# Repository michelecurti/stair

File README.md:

# stair

Switch on a stair that for every step has a strip led, 
controlled in PWM.
All this to generate a stair "wave effect" for my sister.

## project structure

under hw there is the hardware
under fw there is the firmware

Meh..

## software requirements

I worked on OpenBSD.

For the hardware I used Kicad, for the firmware, vim + Makefile..

The toolchain is arm-none-eabi-gcc-linaro.

The "core" is the STM32 BluePill, some shift registers and some
mosfets..

To debug the board I used the st-link with openocd.

## how to compile

$ cd fw/stair/
$ make

## how to debug

$ make debug

## image

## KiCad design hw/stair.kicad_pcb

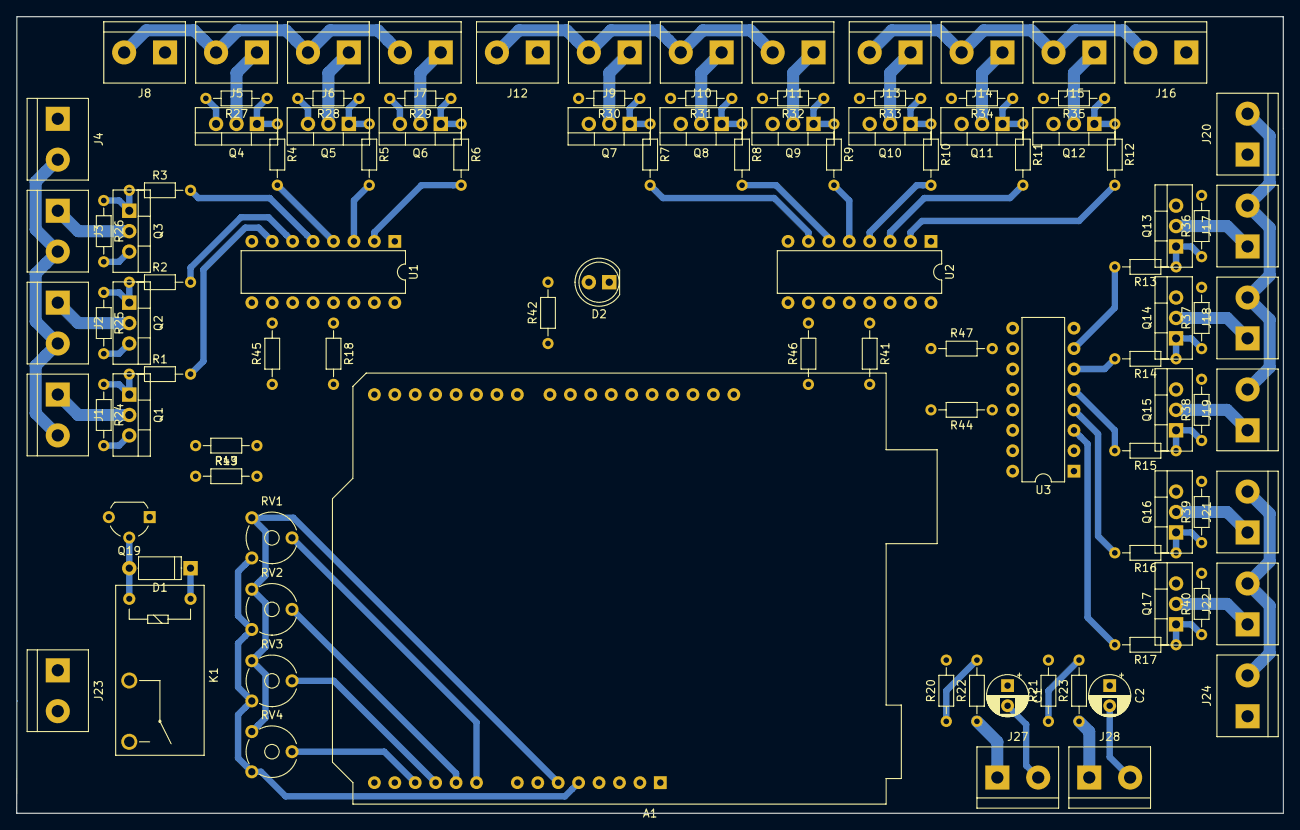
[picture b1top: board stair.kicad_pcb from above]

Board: 2 copper layers, 157.5 x 99.1 mm, 104 parts (0 on the bottom side), 87 nets.

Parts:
A1: AR; Arduino_UNO_R3
C1, C2: C; CP_Radial_D5.0mm_P2.50mm
D1: D; D_A-405_P7.62mm_Horizontal
D2: LED; LED_D5.0mm
J1: M1; TerminalBlock_bornier-2_P5.08mm
J2: M2; TerminalBlock_bornier-2_P5.08mm
J3, J17: M3; TerminalBlock_bornier-2_P5.08mm
J4: P1; TerminalBlock_bornier-2_P5.08mm
J5: M4; TerminalBlock_bornier-2_P5.08mm
J6: M5; TerminalBlock_bornier-2_P5.08mm
J7: M6; TerminalBlock_bornier-2_P5.08mm
J8: P2; TerminalBlock_bornier-2_P5.08mm
J9: M7; TerminalBlock_bornier-2_P5.08mm
J10: M8; TerminalBlock_bornier-2_P5.08mm
J11: M9; TerminalBlock_bornier-2_P5.08mm
J12: P3; TerminalBlock_bornier-2_P5.08mm
J13: M10; TerminalBlock_bornier-2_P5.08mm
J14: M11; TerminalBlock_bornier-2_P5.08mm
J15: M12; TerminalBlock_bornier-2_P5.08mm
J16: P4; TerminalBlock_bornier-2_P5.08mm
J18: M14; TerminalBlock_bornier-2_P5.08mm
J19: M15; TerminalBlock_bornier-2_P5.08mm
J20: P5; TerminalBlock_bornier-2_P5.08mm
J21: M16; TerminalBlock_bornier-2_P5.08mm
J22: M17; TerminalBlock_bornier-2_P5.08mm
J23: MR1; TerminalBlock_bornier-2_P5.08mm
J24: P6; TerminalBlock_bornier-2_P5.08mm
J27: MB2; TerminalBlock_bornier-2_P5.08mm
J28: MB1; TerminalBlock_bornier-2_P5.08mm
K1: G5Q-1A; Relay_SPST_OMRON-G5Q
Q1, Q2, Q3, Q4, Q5, Q6, Q7, Q8, Q9, Q10, Q11, Q12, Q13, Q14, Q15, Q16, Q17: IRF540N; TO-220-3_Vertical
Q19: Q_NPN_BCE; TO-92_Wide
R1, R2, R3, R4, R5, R6, R7, R8, R9, R10, R11, R12, R13, R14, R15, R16, R17, R18, R19, R20, R21, R22, R23, R24, R25, R26, R27, R28, R29, R30, R31, R32, R33, R34, R35, R36, R37, R38, R39, R40, R41, R42, R43, R44, R45, R46, R47: R; R_Axial_DIN0204_L3.6mm_D1.6mm_P7.62mm_Horizontal
RV1, RV2, RV3, RV4: 10K; Potentiometer_Trimmer_Piher_PT-6v_Horizontal
U1, U2, U3: 74HC595; DIP-16_W7.62mm

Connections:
+5V: A1.5, D1.1, K1.5, R45.1, R46.1, R47.1, RV1.1, RV2.1, RV3.1, RV4.1, U1.16, U2.16, U3.16
BTN1: A1.24, R20.2
BTN2: A1.25, R21.2
CKO: A1.26, U1.12, U2.12, U3.12
CLK: A1.28, U1.11, U2.11, U3.11
GND: A1.6, A1.7, A1.29, C1.2, C2.2, D2.1, J4.1, J8.1, J12.1, J16.1, J20.1, J24.1, J27.2, J28.2, Q1.3, Q2.3, Q3.3, Q4.3, Q5.3, Q6.3, Q7.3, Q8.3, Q9.3, Q10.3, Q11.3, Q12.3, Q13.3, Q14.3, Q15.3, Q16.3, Q17.3, Q19.3, R18.2, R24.2, R25.2, R26.2, R27.2, R28.2, R29.2, R30.2, R31.2, R32.2, R33.2, R34.2, R35.2, R36.2, R37.2, R38.2, R39.2, R40.2, R41.2, R43.1, R44.2, RV1.3, RV2.3, RV3.3, RV4.3, U1.8, U2.8, U3.8
LED1: R1.2, U1.7
LED2: R2.2, U1.6
LED3: R3.2, U1.5
LED4: R4.2, U1.4
LED5: R5.2, U1.3
LED6: R6.2, U1.2
LED7: R7.2, U2.7
LED8: R8.2, U2.6
LED9: R9.2, U2.5
LED10: R10.2, U2.4
LED11: R11.2, U2.3
LED12: R12.2, U2.2
LED13: R13.2, U3.7
LED14: R14.2, U3.6
LED15: R15.2, U3.5
LED16: R16.2, U3.4
LED17: R17.2, U3.3
MAX_PWM: A1.12, RV4.2
MOSI: A1.27, U1.14
unnamed: C1.1, R20.1, R22.2
unnamed: C2.1, R21.1, R23.2
unnamed: D1.2, K1.1, Q19.2
unnamed: D2.2, R42.2
unnamed: J1.1, Q1.2
unnamed: J1.2, J2.2, J3.2, J4.2
unnamed: J2.1, Q2.2
unnamed: J3.1, Q3.2
unnamed: J5.1, Q4.2
unnamed: J5.2, J6.2, J7.2, J8.2
unnamed: J6.1, Q5.2
unnamed: J7.1, Q6.2
unnamed: J9.1, Q7.2
unnamed: J10.1, Q8.2
unnamed: J9.2, J10.2, J11.2, J12.2
unnamed: J11.1, Q9.2
unnamed: J13.1, Q10.2
unnamed: J13.2, J14.2, J15.2, J16.2
unnamed: J14.1, Q11.2
unnamed: J15.1, Q12.2
unnamed: J17.1, Q13.2
unnamed: J17.2, J18.2, J19.2, J20.2
unnamed: J18.1, Q14.2
unnamed: J19.1, Q15.2
unnamed: J21.1, Q16.2
unnamed: J21.2, J22.2, J24.2
unnamed: J22.1, Q17.2
unnamed: J23.1, K1.2
unnamed: J23.2, K1.3
unnamed: J27.1, R22.1
unnamed: J28.1, R23.1
unnamed: Q1.1, R1.1, R24.1
unnamed: Q2.1, R2.1, R25.1
unnamed: Q3.1, R3.1, R26.1
unnamed: Q4.1, R4.1, R27.1
unnamed: Q5.1, R5.1, R28.1
unnamed: Q6.1, R6.1, R29.1
unnamed: Q7.1, R7.1, R30.1
unnamed: Q8.1, R8.1, R31.1
unnamed: Q9.1, R9.1, R32.1
unnamed: Q10.1, R10.1, R33.1
unnamed: Q11.1, R11.1, R34.1
unnamed: Q12.1, R12.1, R35.1
unnamed: Q13.1, R13.1, R36.1
unnamed: Q14.1, R14.1, R37.1
unnamed: Q15.1, R15.1, R38.1
unnamed: Q16.1, R16.1, R39.1
unnamed: Q17.1, R17.1, R40.1
unnamed: Q19.1, R19.1, R43.2
unnamed: R18.1, U1.13
unnamed: R41.1, U2.13
unnamed: R44.1, U3.13
unnamed: R45.2, U1.10
unnamed: R46.2, U2.10
unnamed: R47.2, U3.10
unnamed: U1.9, U2.14
unnamed: U2.9, U3.14
RDOWN: A1.10, RV2.2
REL: A1.22, R19.2
RUN: A1.23, R42.1
RUP: A1.9, RV1.2
TIME_ON: A1.11, RV3.2

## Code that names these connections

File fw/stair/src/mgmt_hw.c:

#include <string.h>
#include "stm32f1xx_hal.h"
#include "mgmt_hw.h"
#include "app.h"

#define ADC_CHS		(5)

/* buttons pins */
#define BTNX_GPIO_Port 	GPIOB
#define BTN1_Pin 	GPIO_PIN_0
#define BTN2_Pin 	GPIO_PIN_1
/* output pins */
#define LED_Pin 	GPIO_PIN_13
#define LED_GPIO_Port 	GPIOC
#define LDOUT_Pin 	GPIO_PIN_8
#define LDOUT_GPIO_Port GPIOA
#define RELAY_Pin 	GPIO_PIN_9
#define RELAY_GPIO_Port GPIOB
/* SPI pins*/

static volatile uint32_t ticks;
static uint8_t curr_adc;
static uint32_t adc_vals[ADC_CHS];

static const uint16_t counters[] = 
{
	160, 176, 193, 212, 232, 255, 280, 307, 338, 371, 407, 447, 
	490, 538, 591, 649, 712, 782, 858, 942, 1034, 1135, 1246, 
	1368, 1502, 1649, 1810, 1987, 2182, 2395, 2629, 2886, 3169, 
	3479, 3819, 4192, 4602, 5052, 5546, 6089, 6684, 7338, 8056, 
	8844, 9709, 10658, 11701, 12845, 14101, 15480, 16994, 
	18656, 20481, 22484, 24683, 27097, 29747, 32656, 35850, 
	39356, 43205, 47431, 52070, 57162, 
};

#define MAX_PWM		(sizeof(counters)/sizeof(counters[0]))

static uint8_t irq_cnt;
uint32_t pwms[LEDS_CNT];

static void Error_Handler(void)
{
	for (;;);
}

static void SystemClock_Config(void)
{
	RCC_OscInitTypeDef RCC_OscInitStruct = {0};
	RCC_ClkInitTypeDef RCC_ClkInitStruct = {0};
	RCC_PeriphCLKInitTypeDef PeriphClkInit = {0};

	/* Initializes the CPU, AHB and APB busses clocks */
	RCC_OscInitStruct.OscillatorType = RCC_OSCILLATORTYPE_HSE;
	RCC_OscInitStruct.HSEState = RCC_HSE_ON;
	RCC_OscInitStruct.HSEPredivValue = RCC_HSE_PREDIV_DIV1;
	RCC_OscInitStruct.HSIState = RCC_HSI_ON;
	RCC_OscInitStruct.PLL.PLLState = RCC_PLL_ON;
	RCC_OscInitStruct.PLL.PLLSource = RCC_PLLSOURCE_HSE;
	RCC_OscInitStruct.PLL.PLLMUL = RCC_PLL_MUL8;

	if (HAL_RCC_OscConfig(&RCC_OscInitStruct) != HAL_OK)
	{
		Error_Handler();
	}

	/* Initializes the CPU, AHB and APB busses clocks */
	RCC_ClkInitStruct.ClockType = RCC_CLOCKTYPE_HCLK |
		RCC_CLOCKTYPE_SYSCLK | RCC_CLOCKTYPE_PCLK1 | 
		RCC_CLOCKTYPE_PCLK2;
	RCC_ClkInitStruct.SYSCLKSource = RCC_SYSCLKSOURCE_PLLCLK;
	RCC_ClkInitStruct.AHBCLKDivider = RCC_SYSCLK_DIV1;
	RCC_ClkInitStruct.APB1CLKDivider = RCC_HCLK_DIV2;
	RCC_ClkInitStruct.APB2CLKDivider = RCC_HCLK_DIV1;

	if (HAL_RCC_ClockConfig(&RCC_ClkInitStruct, 
				FLASH_LATENCY_2) != HAL_OK)
	{
		Error_Handler();
	}

	PeriphClkInit.PeriphClockSelection = RCC_PERIPHCLK_ADC;
	PeriphClkInit.AdcClockSelection = RCC_ADCPCLK2_DIV4;

	if (HAL_RCCEx_PeriphCLKConfig(&PeriphClkInit) != HAL_OK)
	{
		Error_Handler();
	}
}

static void MX_SPI2_Init(void)
{
	/* enable clock */
	__HAL_RCC_SPI2_CLK_ENABLE();

	/* disable SPI2 */
	SPI2->CR1 &= SPI_CR1_SPE;

	/* set prescaler */
	SPI2->CR1 |= SPI_BAUDRATEPRESCALER_4;

	/* master mode */
	SPI2->CR1 |= SPI_MODE_MASTER;

	/* do not use slave select */
	SPI2->CR1 |= SPI_CR1_SSM;
	//SPI2->CR1 &= ~SPI_CR1_SSI;

	/* enable SPI2 */
	SPI2->CR1 |= SPI_CR1_SPE;
}

static void MX_GPIO_Init(void)
{
	GPIO_InitTypeDef GPIO_InitStruct = { 0 };

	/* GPIO Ports Clock Enable */
	__HAL_RCC_GPIOA_CLK_ENABLE();
	__HAL_RCC_GPIOB_CLK_ENABLE();
	__HAL_RCC_GPIOC_CLK_ENABLE();
	__HAL_RCC_GPIOD_CLK_ENABLE();

	/*Configure GPIO pin Output Level */
	HAL_GPIO_WritePin(LED_GPIO_Port, LED_Pin, GPIO_PIN_SET);

	/*Configure GPIO pin Output Level */
	HAL_GPIO_WritePin(LDOUT_GPIO_Port, LDOUT_Pin, GPIO_PIN_RESET);

	/*Configure GPIO pin : LED_Pin */
	GPIO_InitStruct.Pin = LED_Pin;
	GPIO_InitStruct.Mode = GPIO_MODE_OUTPUT_PP;
	GPIO_InitStruct.Pull = GPIO_NOPULL;
	GPIO_InitStruct.Speed = GPIO_SPEED_FREQ_LOW;
	HAL_GPIO_Init(LED_GPIO_Port, &GPIO_InitStruct);

	/*Configure GPIO pin : RELAY_Pin */
	GPIO_InitStruct.Pin = RELAY_Pin;
	GPIO_InitStruct.Mode = GPIO_MODE_OUTPUT_PP;
	GPIO_InitStruct.Pull = GPIO_NOPULL;
	GPIO_InitStruct.Speed = GPIO_SPEED_FREQ_LOW;
	HAL_GPIO_Init(RELAY_GPIO_Port, &GPIO_InitStruct);

	/*Configure GPIO pin : LDOUT_Pin  */
	GPIO_InitStruct.Pin = LDOUT_Pin;
	GPIO_InitStruct.Mode = GPIO_MODE_OUTPUT_PP;
	GPIO_InitStruct.Pull = GPIO_NOPULL;
	GPIO_InitStruct.Speed = GPIO_SPEED_FREQ_LOW;
	HAL_GPIO_Init(LDOUT_GPIO_Port, &GPIO_InitStruct);

	/*Configure GPIO pins : BTN1_Pin BTN2_Pin */
	GPIO_InitStruct.Pin = BTN1_Pin | BTN2_Pin;
	GPIO_InitStruct.Mode = GPIO_MODE_INPUT;
	GPIO_InitStruct.Pull = GPIO_PULLUP;
	HAL_GPIO_Init(BTNX_GPIO_Port, &GPIO_InitStruct);
	
	/* configure ADC pins */
	memset(&GPIO_InitStruct, 0, sizeof(GPIO_InitStruct));
	GPIO_InitStruct.Pin = GPIO_PIN_0 | GPIO_PIN_1 | GPIO_PIN_2 |
		GPIO_PIN_3 | GPIO_PIN_4;
	GPIO_InitStruct.Mode = GPIO_MODE_ANALOG;
	GPIOA->CRL &= 0xFFFFFC00;
	//HAL_GPIO_Init(GPIOA, &GPIO_InitStruct);

	/* configure SPI pins */
	GPIO_InitStruct.Pin = GPIO_PIN_13 | GPIO_PIN_15;
	GPIO_InitStruct.Mode = GPIO_MODE_AF_PP;
	GPIO_InitStruct.Speed = GPIO_SPEED_FREQ_HIGH;
	HAL_GPIO_Init(GPIOB, &GPIO_InitStruct);
}

static void MX_ADC1_Init(void)
{
	__HAL_RCC_ADC1_CLK_ENABLE();

	ADC1->CR2 |= ADC_CR2_ADON;
	while((ADC1->CR2 | ADC_CR2_ADON) == 0);
	ADC1->CR2 |= ADC_CR2_EXTSEL;

	ADC1->SMPR1 = 0x7FFFFFFF;
	ADC1->SMPR2 = 0xCFFFFFFF;
}

static void pwm_timer_init(void)
{
	/* enable clock */
	__HAL_RCC_TIM4_CLK_ENABLE();

	/* set prescaler */
	TIM4->PSC = 0;

	/* schedule first timer interrupt */
	TIM4->ARR = 0xFFFE;

	/* enable counter */
	TIM4->CR1 |= TIM_CR1_CEN;

	/* enable counter interrupt */
	TIM4->DIER |= TIM_DIER_UIE;

	/* enable TIM4 interrupt */
	NVIC_EnableIRQ(TIM4_IRQn);
}

void SysTick_Handler (void)
{
	HAL_IncTick();
}

void mgmt_hw_init(void)
{
	SystemClock_Config();
	//SystickInit(APP_TICK_FREQ);
	HAL_Init();
	MX_GPIO_Init();
	MX_SPI2_Init();
	MX_ADC1_Init();
	pwm_timer_init();
}

void mgmt_hw_fsm(void)
{
	static uint32_t old;
	uint32_t tick;

	tick = HAL_GetTick() / 50;

	if (tick != old)
	{
		old = tick;

		adc_vals[curr_adc] = (adc_vals[curr_adc] + ADC1->DR) / 2;

		if (++curr_adc >= ADC_CHS)
		{
			curr_adc = 0;
		}

		ADC1->SQR3 = (curr_adc << (0 * 5));
		ADC1->CR2 |= ADC_CR2_SWSTART;
		ADC1->CR2 &= ~ADC_CR2_SWSTART;
	}
}

/* 
 * macro to set the PWM PIN output
 * p is the PWM index
 * b is the byte in tx buffer (the shift register index)
 * i is the bit index of the byte
 */
#define SET_OUT(p, b, i)		\
	if (irq_cnt < pwms[(p)]) 		\
	 buff[(b)] |= (1 << (i)); else\
	 buff[(b)] &= ~(1 << (i))

void __attribute__ ((optimize ("O3"))) TIM4_IRQHandler(void)
//void TIM4_IRQHandler(void)
{
	uint8_t next;
	static uint8_t buff[3];

	/* clear the interrupt flag */
	TIM4->SR &= 0xFFFFFE;

	/* schedule the next timer interrupt asap */
	next = irq_cnt + 1;

	if (next >= MAX_PWM)
	{
		next = 0;
	}

	TIM4->ARR = counters[next];

	/* Set the LEDs output 
	 *
	 * This loop has been unrolled to be fast, it's CPU 
	 * time spent is very predictable.
	 * One can choose the shift register output PIN here,
	 * I have 17 pwm outputs, so I use 6 pins of the
	 * first shift register, 6 of the second and 5 of the
	 * third.
	 * I'm using the 74HC595, so I do not use the Qa pin
	 * because it's on the other side of the DIP package 
	 * and the routing will be complicated for nothing :p
	 */
	SET_OUT(0, 0, 3);
	SET_OUT(1, 0, 4);
	SET_OUT(2, 0, 5);
	SET_OUT(3, 0, 6);
	SET_OUT(4, 0, 7);

	SET_OUT(5, 1, 2);
	SET_OUT(6, 1, 3);
	SET_OUT(7, 1, 4);
	SET_OUT(8, 1, 5);
	SET_OUT(9, 1, 6);
	SET_OUT(10, 1, 7);

	SET_OUT(11, 2, 2);
	SET_OUT(12, 2, 3);
	SET_OUT(13, 2, 4);
	SET_OUT(14, 2, 5);
	SET_OUT(15, 2, 6);
	SET_OUT(16, 2, 7);

	/* increase irq counter */
	irq_cnt = next;

	/* send spi packet */
	SPI2->DR = buff[2];
	while((SPI2->SR & SPI_SR_TXE) == 0);
	SPI2->DR = buff[1];
	while((SPI2->SR & SPI_SR_TXE) == 0);
	SPI2->DR = buff[0];
	while((SPI2->SR & SPI_SR_BSY) != 0);

	/* generate clock pulse */
	HAL_GPIO_WritePin(LDOUT_GPIO_Port, LDOUT_Pin, GPIO_PIN_RESET);
	HAL_GPIO_WritePin(LDOUT_GPIO_Port, LDOUT_Pin, GPIO_PIN_SET);
	HAL_GPIO_WritePin(LDOUT_GPIO_Port, LDOUT_Pin, GPIO_PIN_RESET);
}

uint8_t mgmt_hw_get_button(uint8_t id)
{
	uint8_t val;

	switch (id)
	{
	case 0:
		val = HAL_GPIO_ReadPin(BTNX_GPIO_Port, BTN1_Pin);
		break;
	case 1:
		val = HAL_GPIO_ReadPin(BTNX_GPIO_Port, BTN2_Pin);
		break;

	default:
		val = GPIO_PIN_SET;
	}

	return val == GPIO_PIN_RESET;
}

uint32_t mgmt_hw_get_app_tick(void)
{
	return HAL_GetTick() / 10;
}

void mgmt_hw_led_status(uint8_t state)
{
	HAL_GPIO_WritePin(LED_GPIO_Port, LED_Pin, 
			state ? GPIO_PIN_RESET : GPIO_PIN_SET);
}

uint8_t mgmt_hw_get_adc(enum mgmt_hw_adc_e idx)
{
	uint32_t val;

	switch (idx)
	{
	case ADC_STAIR_TIME:
		val = adc_vals[0];
		break;

	case ADC_STEP_TIME:
		val = adc_vals[1];
		break;

	case ADC_RAMP_ON:
		val = adc_vals[2];
		break;

	case ADC_RAMP_OFF:
		val = adc_vals[3];
		break;

	case ADC_PWM_MAX:
		val = adc_vals[4];
		break;

	default:
		val = 0;
		break;
	}

	return val >> 4;
}

void mgmt_hw_set_relay(uint8_t state)
{
	HAL_GPIO_WritePin(RELAY_GPIO_Port, RELAY_Pin, 
			state ? GPIO_PIN_SET : GPIO_PIN_RESET);
}

uint8_t mgmt_hw_get_max_pwm(void)
{
	return MAX_PWM + 1;
}

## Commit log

2020-10-20 add image and pdf
